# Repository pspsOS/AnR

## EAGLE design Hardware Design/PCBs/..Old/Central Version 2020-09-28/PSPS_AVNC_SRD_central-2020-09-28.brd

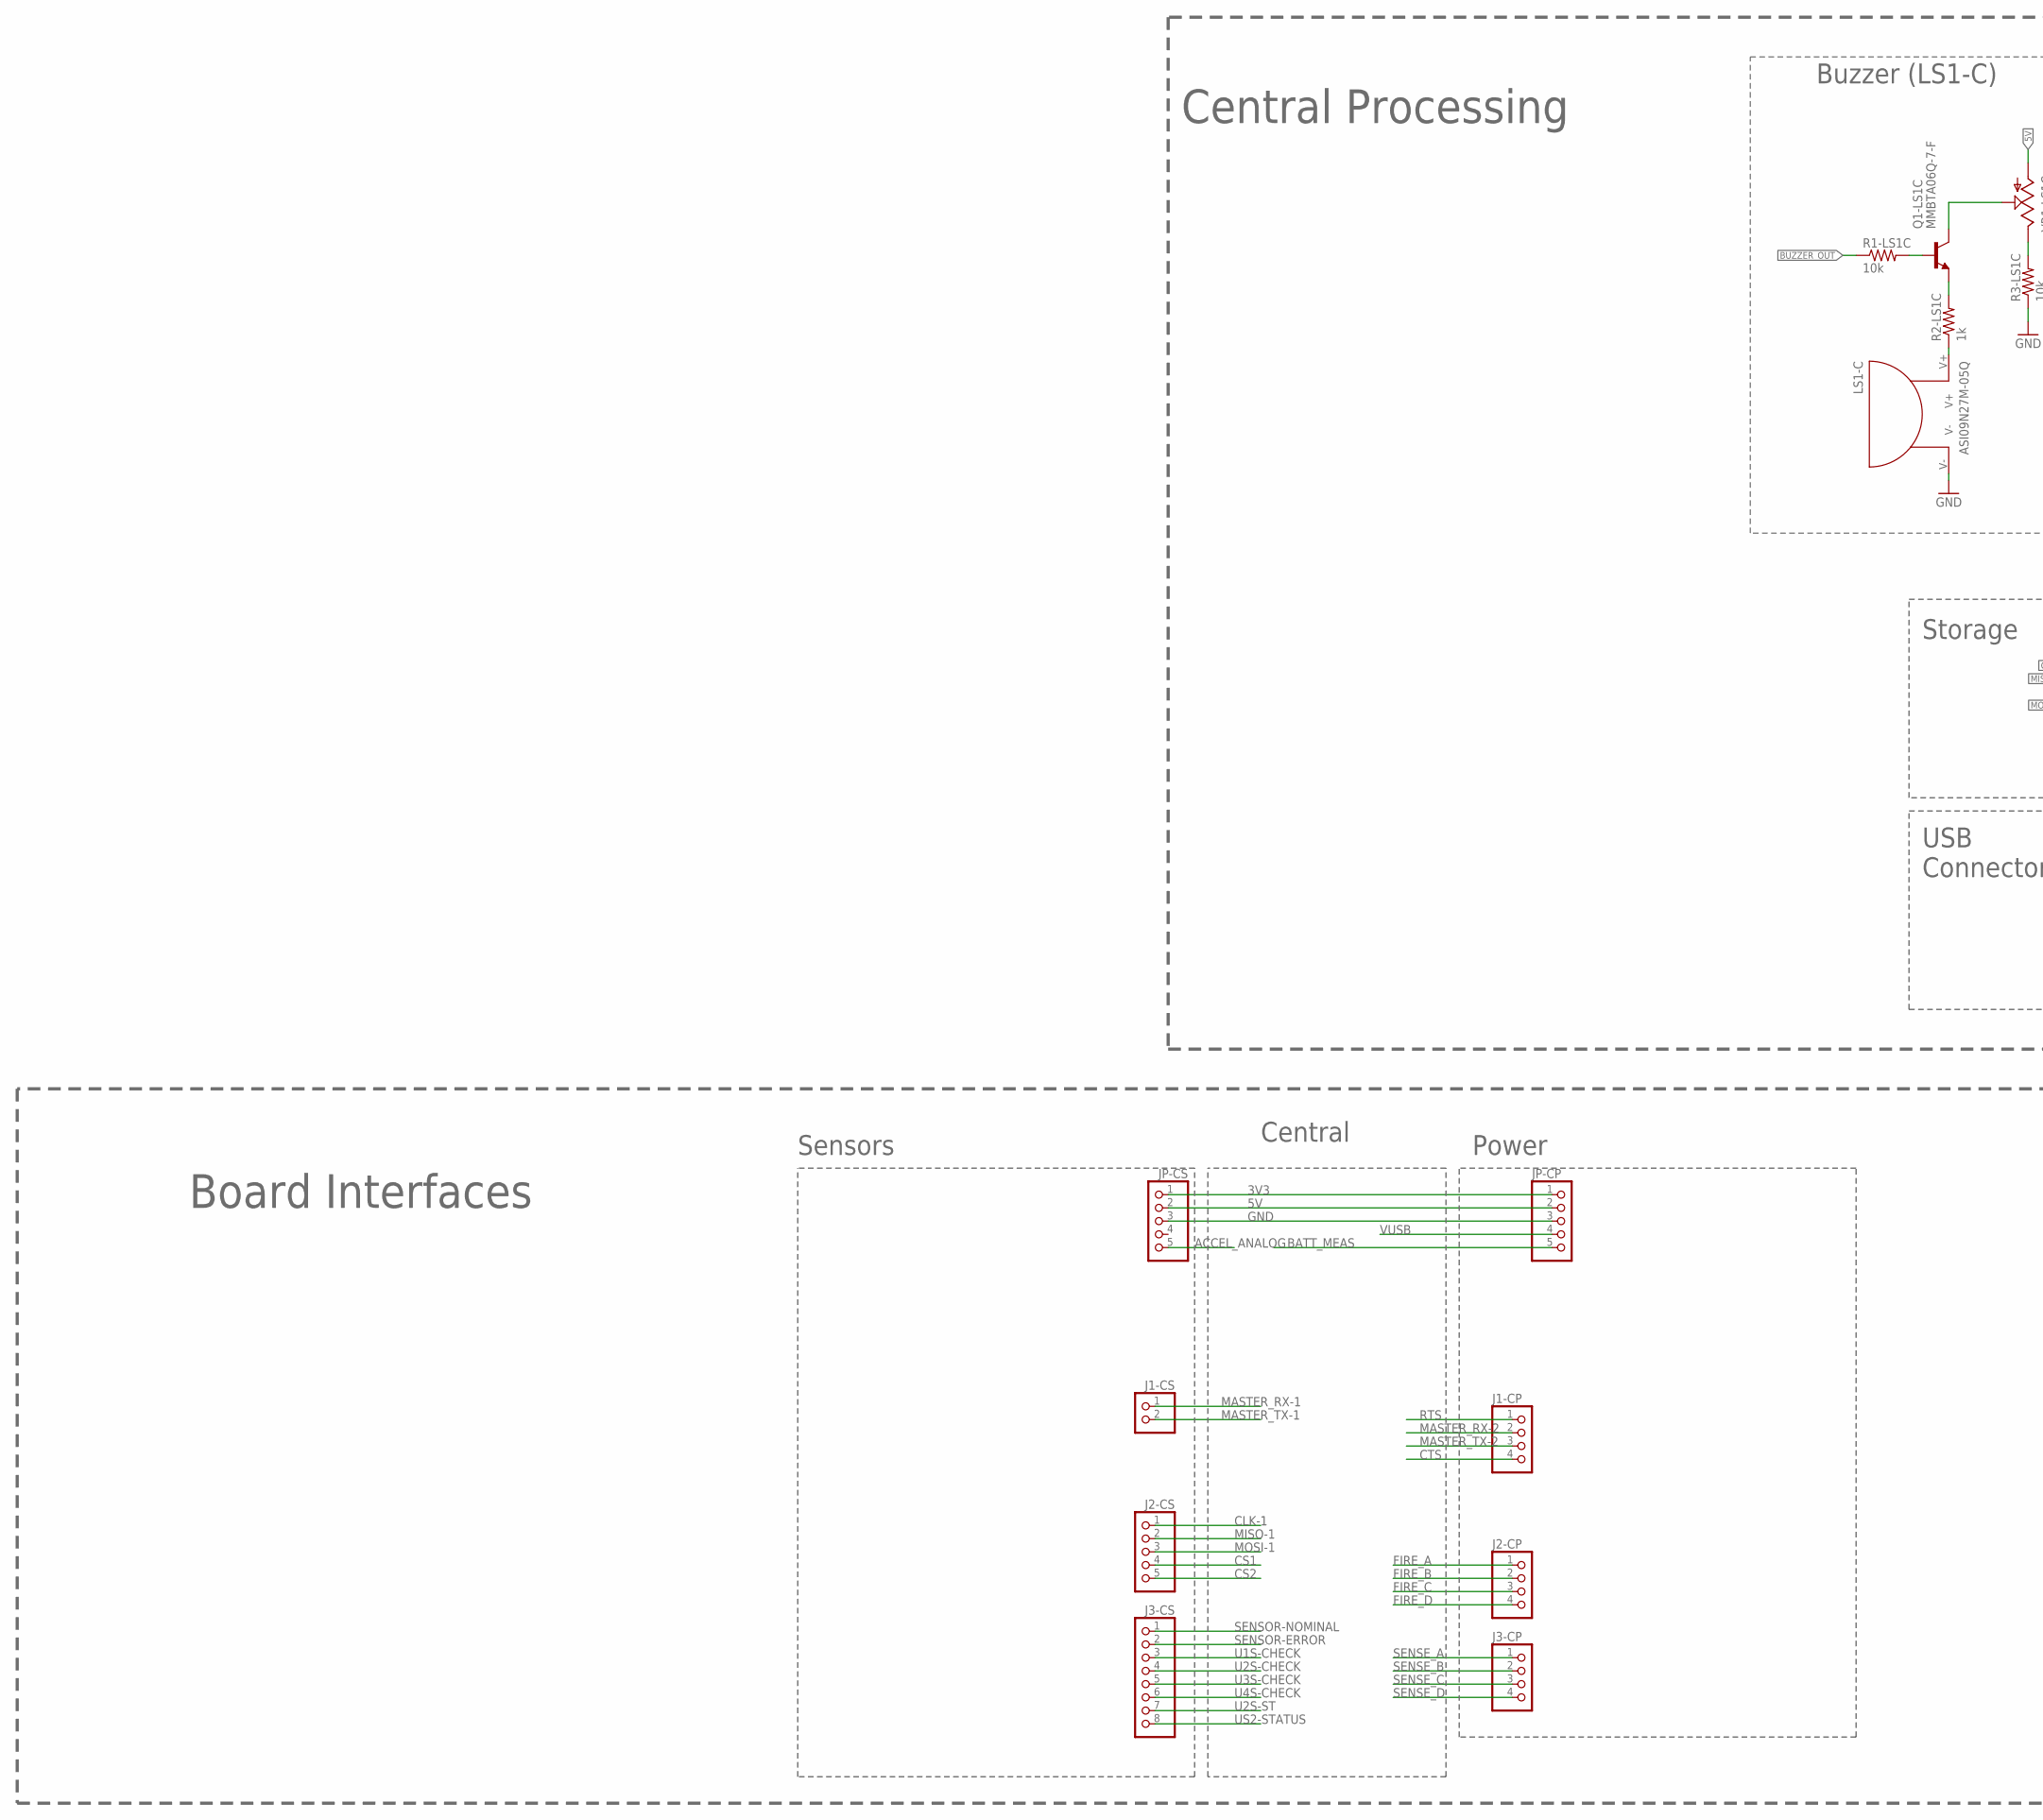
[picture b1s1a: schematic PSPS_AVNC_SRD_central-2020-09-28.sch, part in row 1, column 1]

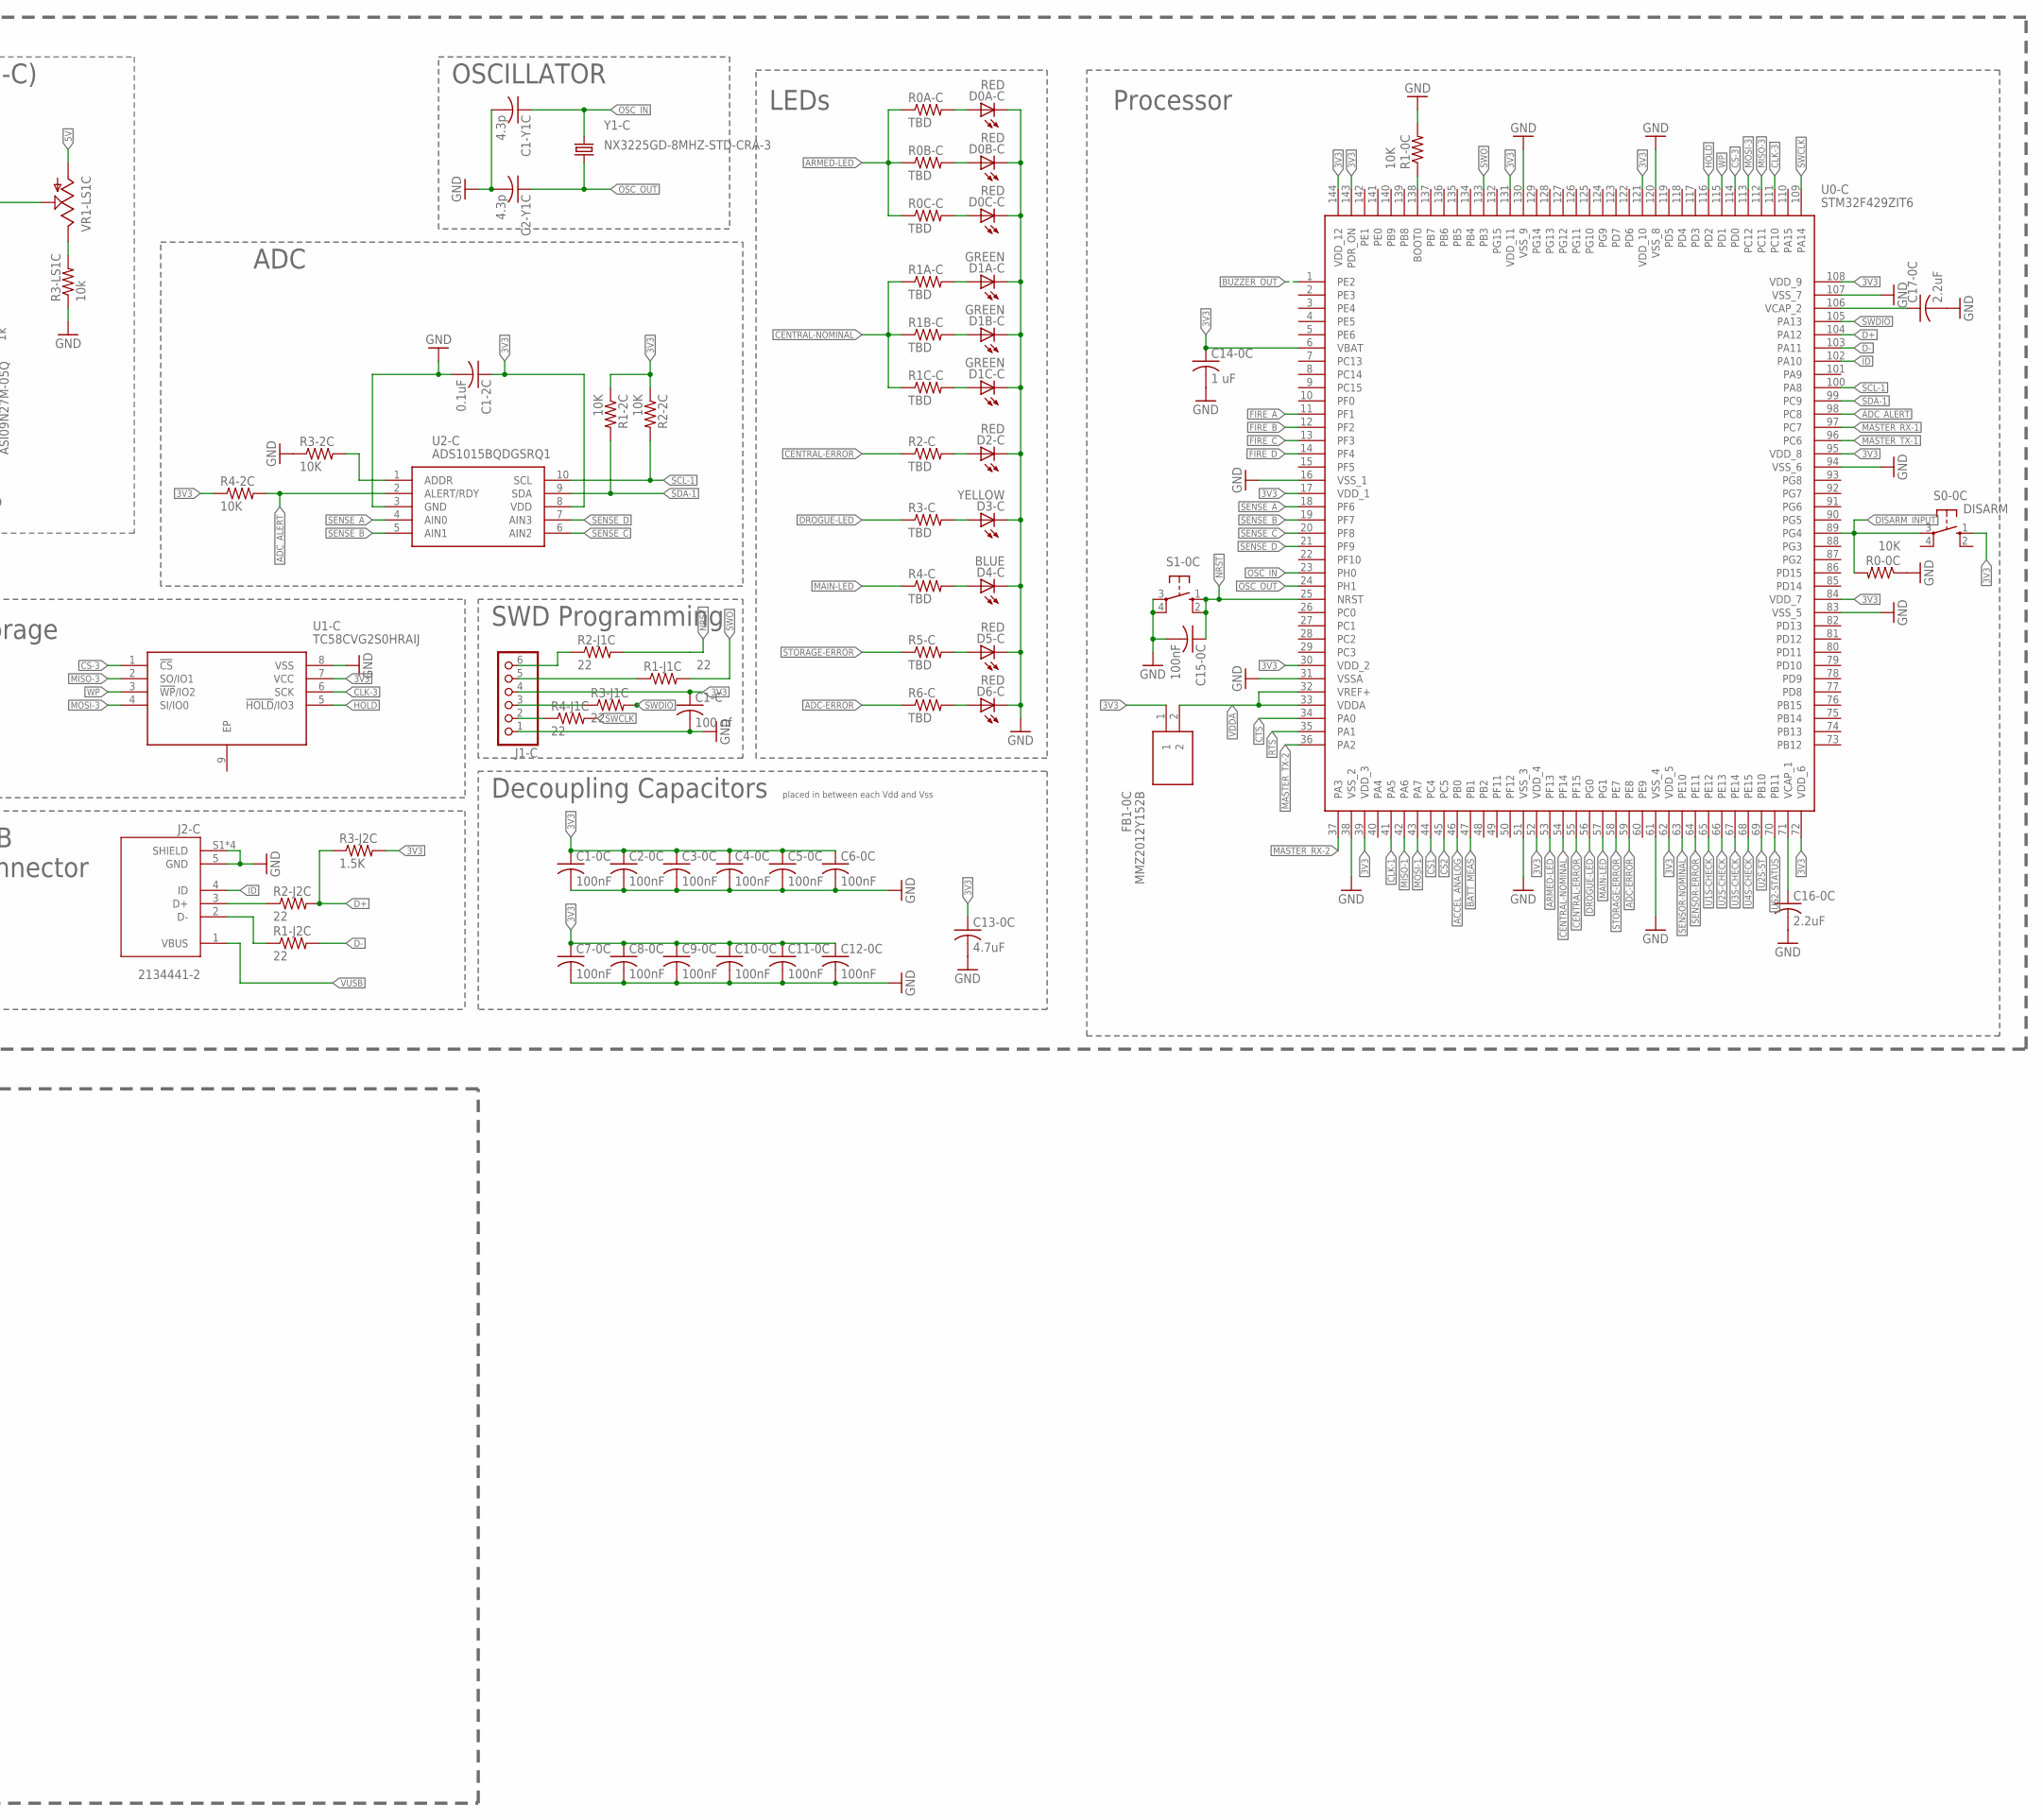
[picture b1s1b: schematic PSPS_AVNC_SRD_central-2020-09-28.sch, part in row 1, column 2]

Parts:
C1-0C, C2-0C, C3-0C, C4-0C, C5-0C, C6-0C, C7-0C, C8-0C, C9-0C, C10-0C, C11-0C, C12-0C, C15-0C: 100nF; C0805
C1-2C: 0.1uF; C0805
C1-C: 100 nf; C0805
C1-Y1C, C2-Y1C: 4.3p; C0805
C13-0C: 4.7uF; C0805
C14-0C: 1 uF; C0805
C16-0C, C17-0C: 2.2uF; C0805
D0A-C, D0B-C, D0C-C, D2-C, D5-C, D6-C: RED; CHIPLED_0805
D1A-C, D1B-C, D1C-C: GREEN; CHIPLED_0805
D3-C: YELLOW; CHIPLED_0805
D4-C: BLUE; CHIPLED_0805
FB1-0C: MMZ2012Y152B; BEADC2012X105N
J1-C: PINHD-1X6; 1X06
J1-CP, J2-CP, J3-CP: PINHD-1X4; 1X04
J1-CS: PINHD-1X2; 1X02
J2-C: 2134441-2; TE_2134441-2
J2-CS: PINHD-1X5; 1X05
J3-CS: PINHD-1X8; 1X08
JP-CP: PINHD-1X5; 1X05
JP-CS: PINHD-1X5; 1X05
LS1-C: ASI09N27M-05Q
Q1-LS1C: MMBTA06Q-7-F; SOT23
R0-0C, R1-0C, R1-2C, R2-2C, R3-2C, R4-2C: 10K; R0805
R0A-C, R0B-C, R0C-C, R1A-C, R1B-C, R1C-C, R2-C, R3-C, R4-C, R5-C, R6-C: TBD; M0805
R1-J1C, R1-J2C, R2-J1C, R2-J2C, R3-J1C, R4-J1C: 22; M0805
R1-LS1C, R3-LS1C: 10k; R0805
R2-LS1C: 1k; R0805
R3-J2C: 1.5K; M0805
S0-0C: DISARM; B3F-10XX
S1-0C: 10-XX; B3F-10XX
U0-C: STM32F429ZIT6; QFP50P2200X2200X160-144N
U1-C: TC58CVG2S0HRAIJ; SON127P800X600X80-9N
U2-C: ADS1015BQDGSRQ1; SOP50P490X110-10N
VR1-LS1C: TRIM_US-LI10; LI10
Y1-C: NX3225GD-8MHZ-STD-CRA-3; NX3225GD

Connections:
3V3: C1-0C.1, C1-2C.1, C1-C.1, C2-0C.1, C3-0C.1, C4-0C.1, C5-0C.1, C6-0C.1, C7-0C.1, C8-0C.1, C9-0C.1, C10-0C.1, C11-0C.1, C12-0C.1, C13-0C.1, C14-0C.1, FB1-0C.1, J1-C.4, JP-CP.1, JP-CS.1, R1-2C.1, R2-2C.1, R3-J2C.2, R4-2C.1, S0-0C.1 (S), U0-C.6 (VBAT), U0-C.17 (VDD_1), U0-C.30 (VDD_2), U0-C.39 (VDD_3), U0-C.52 (VDD_4), U0-C.62 (VDD_5), U0-C.72 (VDD_6), U0-C.84 (VDD_7), U0-C.95 (VDD_8), U0-C.108 (VDD_9), U0-C.121 (VDD_10), U0-C.131 (VDD_11), U0-C.143 (PDR_ON), U0-C.144 (VDD_12), U1-C.7 (VCC), U2-C.8 (VDD)
5V: JP-CP.2, JP-CS.2, VR1-LS1C.A
ACCEL_ANALOG: JP-CS.5, U0-C.46 (PB0)
ADC-ERROR: R6-C.1, U0-C.59 (PE8)
ADC_ALERT: R4-2C.2, U0-C.98 (PC8), U2-C.2 (ALERT/RDY)
ADDR: R3-2C.2, U2-C.1 (ADDR)
ARMED-LED: R0A-C.1, R0B-C.1, R0C-C.1, U0-C.53 (PF13)
BATT_MEAS: JP-CP.5, U0-C.47 (PB1)
BOOT0: R1-0C.1, U0-C.138 (BOOT0)
BUZZER_OUT: R1-LS1C.1, U0-C.1 (PE2)
CENTRAL-ERROR: R2-C.1, U0-C.55 (PF15)
CENTRAL-NOMINAL: R1A-C.1, R1B-C.1, R1C-C.1, U0-C.54 (PF14)
CLK-1: J2-CS.1, U0-C.41 (PA5)
CLK-3: U0-C.111 (PC10), U1-C.6 (SCK)
CS1: J2-CS.4, U0-C.44 (PC4)
CS2: J2-CS.5, U0-C.45 (PC5)
CS-3: U0-C.114 (PD0), U1-C.1 (!CS)
CTS: J1-CP.4, U0-C.34 (PA0)
D+: R2-J2C.2, R3-J2C.1, U0-C.104 (PA12)
D+_R2-J1C: J2-C.3 (D+), R2-J2C.1
D-: R1-J2C.2, U0-C.103 (PA11)
D-_R1-J1C: J2-C.2 (D-), R1-J2C.1
DISARM_INPUT: R0-0C.2, S0-0C.3, U0-C.89 (PG4)
DROGUE-LED: R3-C.1, U0-C.56 (PG0)
FIRE_A: J2-CP.1, U0-C.11 (PF1)
FIRE_B: J2-CP.2, U0-C.12 (PF2)
FIRE_C: J2-CP.3, U0-C.13 (PF3)
FIRE_D: J2-CP.4, U0-C.14 (PF4)
GND: C1-0C.2, C1-2C.2, C1-C.2, C1-Y1C.2, C2-0C.2, C2-Y1C.2, C3-0C.2, C4-0C.2, C5-0C.2, C6-0C.2, C7-0C.2, C8-0C.2, C9-0C.2, C10-0C.2, C11-0C.2, C12-0C.2, C13-0C.2, C14-0C.2, C15-0C.2, C16-0C.2, C17-0C.2, D0A-C.C, D0B-C.C, D0C-C.C, D1A-C.C, D1B-C.C, D1C-C.C, D2-C.C, D3-C.C, D4-C.C, D5-C.C, D6-C.C, J1-C.1, J2-C.5 (GND), J2-C.S1 (SHIELD), J2-C.S2 (SHIELD), J2-C.S3 (SHIELD), J2-C.S4 (SHIELD), JP-CP.3, JP-CS.3, LS1-C.V-, R0-0C.1, R1-0C.2, R3-2C.1, R3-LS1C.1, S1-0C.3, S1-0C.4 (P1), U0-C.16 (VSS_1), U0-C.31 (VSSA), U0-C.38 (VSS_2), U0-C.51 (VSS_3), U0-C.61 (VSS_4), U0-C.83 (VSS_5), U0-C.94 (VSS_6), U0-C.107 (VSS_7), U0-C.120 (VSS_8), U0-C.130 (VSS_9), U1-C.8 (VSS), U2-C.3 (GND)
HOLD: U0-C.116 (PD2), U1-C.5 (!HOLD!/IO3)
ID: J2-C.4 (ID), U0-C.102 (PA10)
J1-C_R1-J1C: J1-C.5, R1-J1C.1
J1-C_R2-J1C: J1-C.6, R2-J1C.1
J1-C_R3-J1C: J1-C.3, R3-J1C.1
J1-C_R4-J1C: J1-C.2, R4-J1C.1
MAIN-LED: R4-C.1, U0-C.57 (PG1)
MASTER_RX-1: J1-CS.1, U0-C.97 (PC7)
MASTER_RX-2: J1-CP.2, U0-C.37 (PA3)
MASTER_TX-1: J1-CS.2, U0-C.96 (PC6)
MASTER_TX-2: J1-CP.3, U0-C.36 (PA2)
MISO-1: J2-CS.2, U0-C.42 (PA6)
MISO-3: U0-C.112 (PC11), U1-C.2 (SO/IO1)
MOSI-1: J2-CS.3, U0-C.43 (PA7)
MOSI-3: U0-C.113 (PC12), U1-C.4 (SI/IO0)
NRST: C15-0C.1, R2-J1C.2, S1-0C.1 (S), S1-0C.2 (S1), U0-C.25 (NRST)
OSC_IN: C1-Y1C.1, U0-C.23 (PH0), Y1-C.P$2 (2)
OSC_OUT: C2-Y1C.1, U0-C.24 (PH1), Y1-C.P$1 (1)
Q1-LS1C_R2-LS1C: Q1-LS1C.3 (E), R2-LS1C.2
R0A-C_D0A-C: D0A-C.A, R0A-C.2
R0B-C_D0B-C: D0B-C.A, R0B-C.2
R0C-C_D0C-C: D0C-C.A, R0C-C.2
R1-LS1C_Q1-LS1C: Q1-LS1C.1 (B), R1-LS1C.2
R1A-C_D1A-C: D1A-C.A, R1A-C.2
R1B-C_D1B-C: D1B-C.A, R1B-C.2
R1C-C_D1C-C: D1C-C.A, R1C-C.2
R2-C_D2-C: D2-C.A, R2-C.2
R2-LS1C_LS1-C: LS1-C.V+, R2-LS1C.1
R3-C_D3-C: D3-C.A, R3-C.2
R4-C_D4-C: D4-C.A, R4-C.2
R5-C_D5-C: D5-C.A, R5-C.2
R6-C_D6-C: D6-C.A, R6-C.2
RTS: J1-CP.1, U0-C.35 (PA1)
SCL-1: R2-2C.2, U0-C.100 (PA8), U2-C.10 (SCL)
SDA-1: R1-2C.2, U0-C.99 (PC9), U2-C.9 (SDA)
SENSE_A: J3-CP.1, U0-C.18 (PF6), U2-C.4 (AIN0)
SENSE_B: J3-CP.2, U0-C.19 (PF7), U2-C.5 (AIN1)
SENSE_C: J3-CP.3, U0-C.20 (PF8), U2-C.6 (AIN2)
SENSE_D: J3-CP.4, U0-C.21 (PF9), U2-C.7 (AIN3)
SENSOR-ERROR: J3-CS.2, U0-C.64 (PE11)
SENSOR-NOMINAL: J3-CS.1, U0-C.63 (PE10)
STORAGE-ERROR: R5-C.1, U0-C.58 (PE7)
SWCLK: R4-J1C.2, U0-C.109 (PA14)
SWDIO: R3-J1C.2, U0-C.105 (PA13)
SWO: R1-J1C.2, U0-C.133 (PB3)
U1S-CHECK: J3-CS.3, U0-C.65 (PE12)
U2S-CHECK: J3-CS.4, U0-C.66 (PE13)
U2S-ST: J3-CS.7, U0-C.69 (PB10)
U3S-CHECK: J3-CS.5, U0-C.67 (PE14)
U4S-CHECK: J3-CS.6, U0-C.68 (PE15)
US2-STATUS: J3-CS.8, U0-C.70 (PB11)
VCAP_1: C16-0C.1, U0-C.71 (VCAP_1)
VCAP_2: C17-0C.1, U0-C.106 (VCAP_2)
VDDA: FB1-0C.2, U0-C.32 (VREF+), U0-C.33 (VDDA)
VR1-LS1C: Q1-LS1C.2 (C), VR1-LS1C.S
VR1-LS1C_R3-LS1C: R3-LS1C.2, VR1-LS1C.E
VUSB: J2-C.1 (VBUS), JP-CP.4
WP: U0-C.115 (PD1), U1-C.3 (!WP!/IO2)

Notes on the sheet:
Central Processing
placed in between each Vdd and Vss
Processor
Storage
Decoupling Capacitors
SWD Programming
LEDs
ADC
USB Connector
OSCILLATOR
Buzzer (LS1-C)
Central
Power
Sensors
Board Interfaces

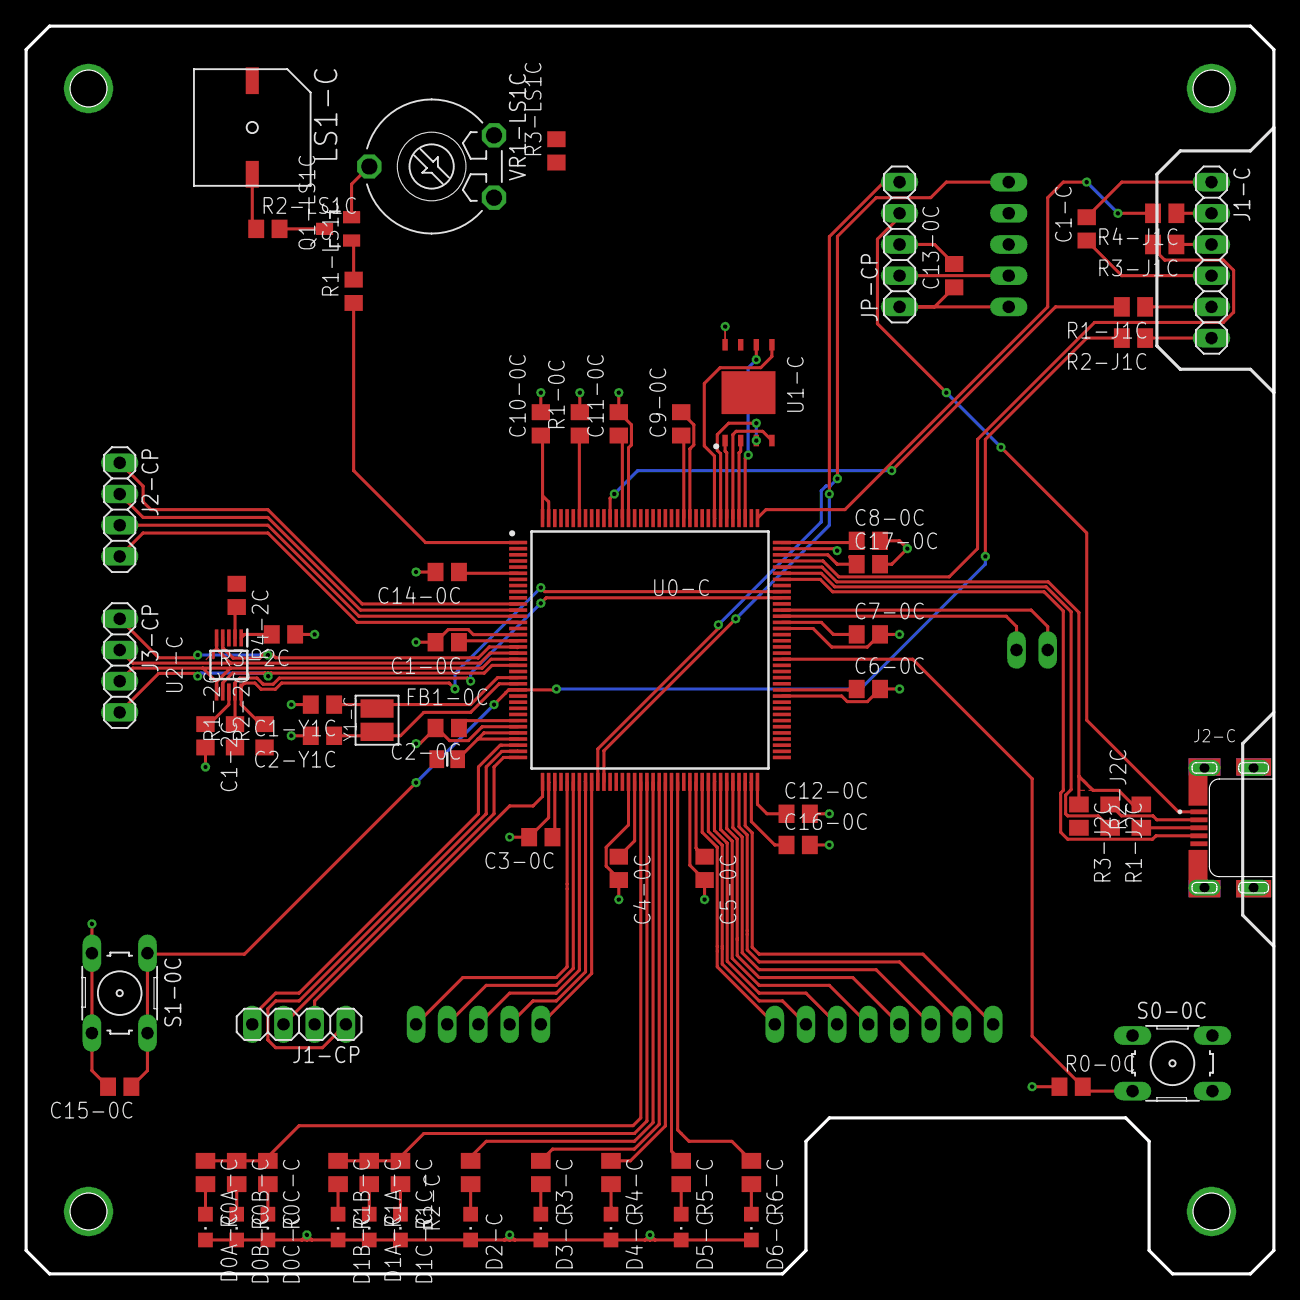
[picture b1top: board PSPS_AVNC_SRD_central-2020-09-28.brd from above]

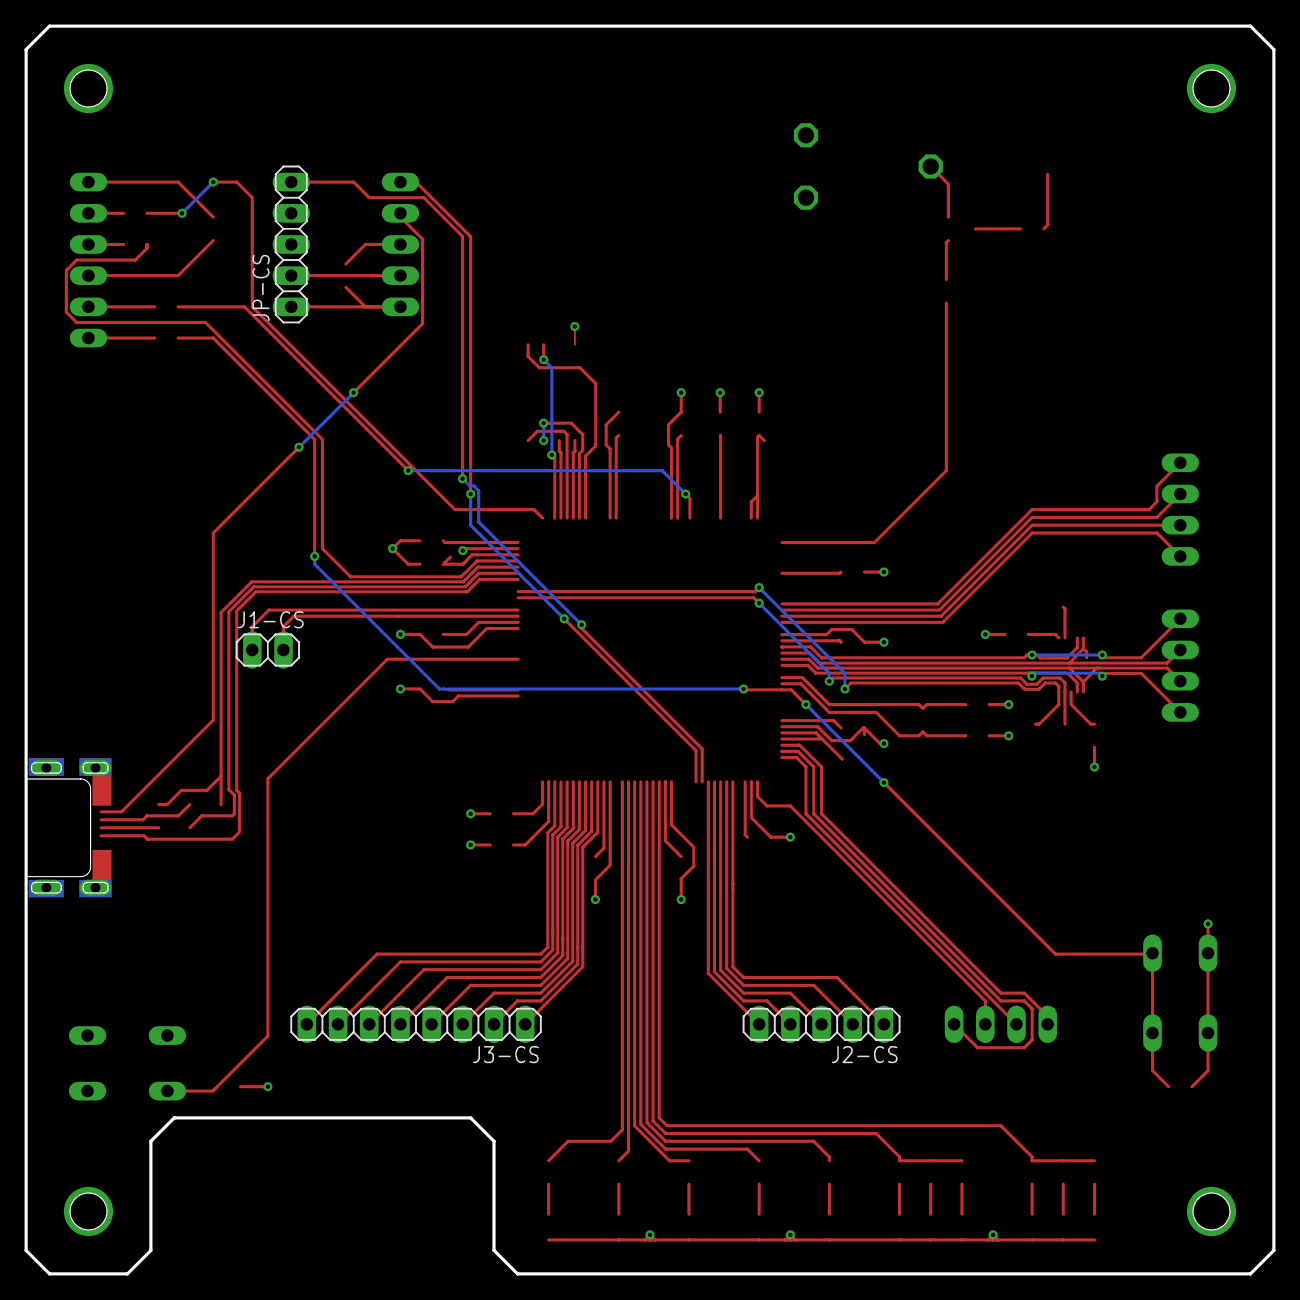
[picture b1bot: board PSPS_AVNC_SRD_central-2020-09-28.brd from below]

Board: 2 copper layers, 101.6 x 101.6 mm, 79 parts (4 on the bottom side), 87 nets.

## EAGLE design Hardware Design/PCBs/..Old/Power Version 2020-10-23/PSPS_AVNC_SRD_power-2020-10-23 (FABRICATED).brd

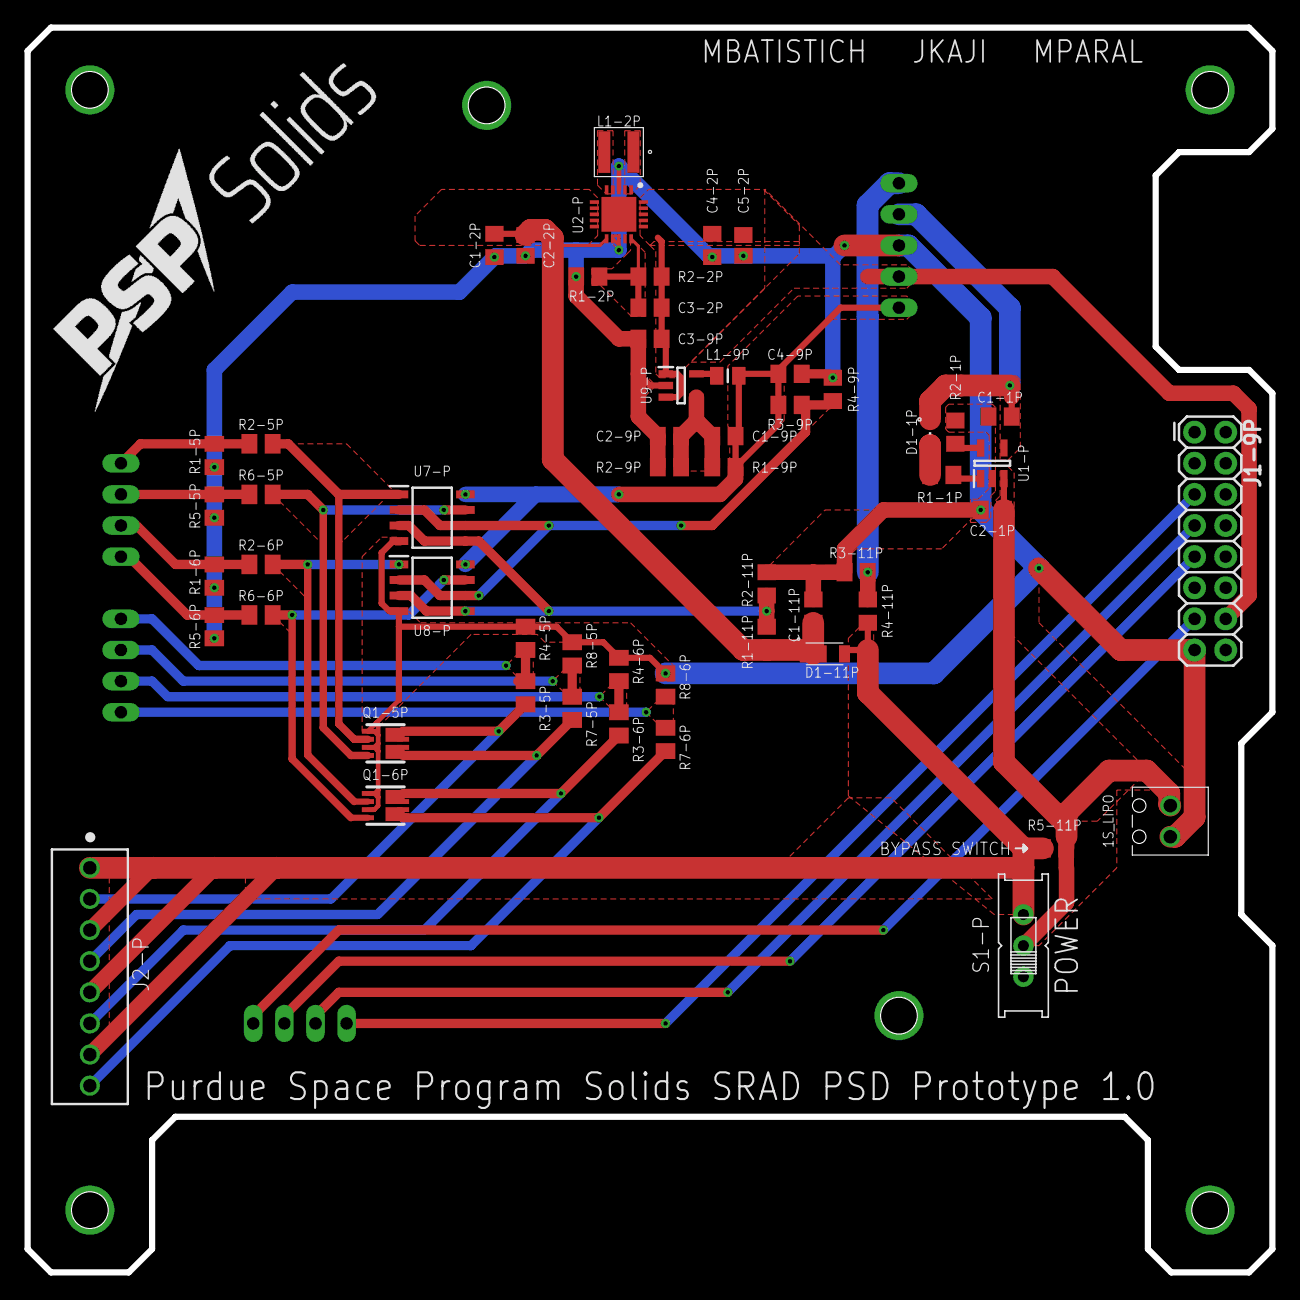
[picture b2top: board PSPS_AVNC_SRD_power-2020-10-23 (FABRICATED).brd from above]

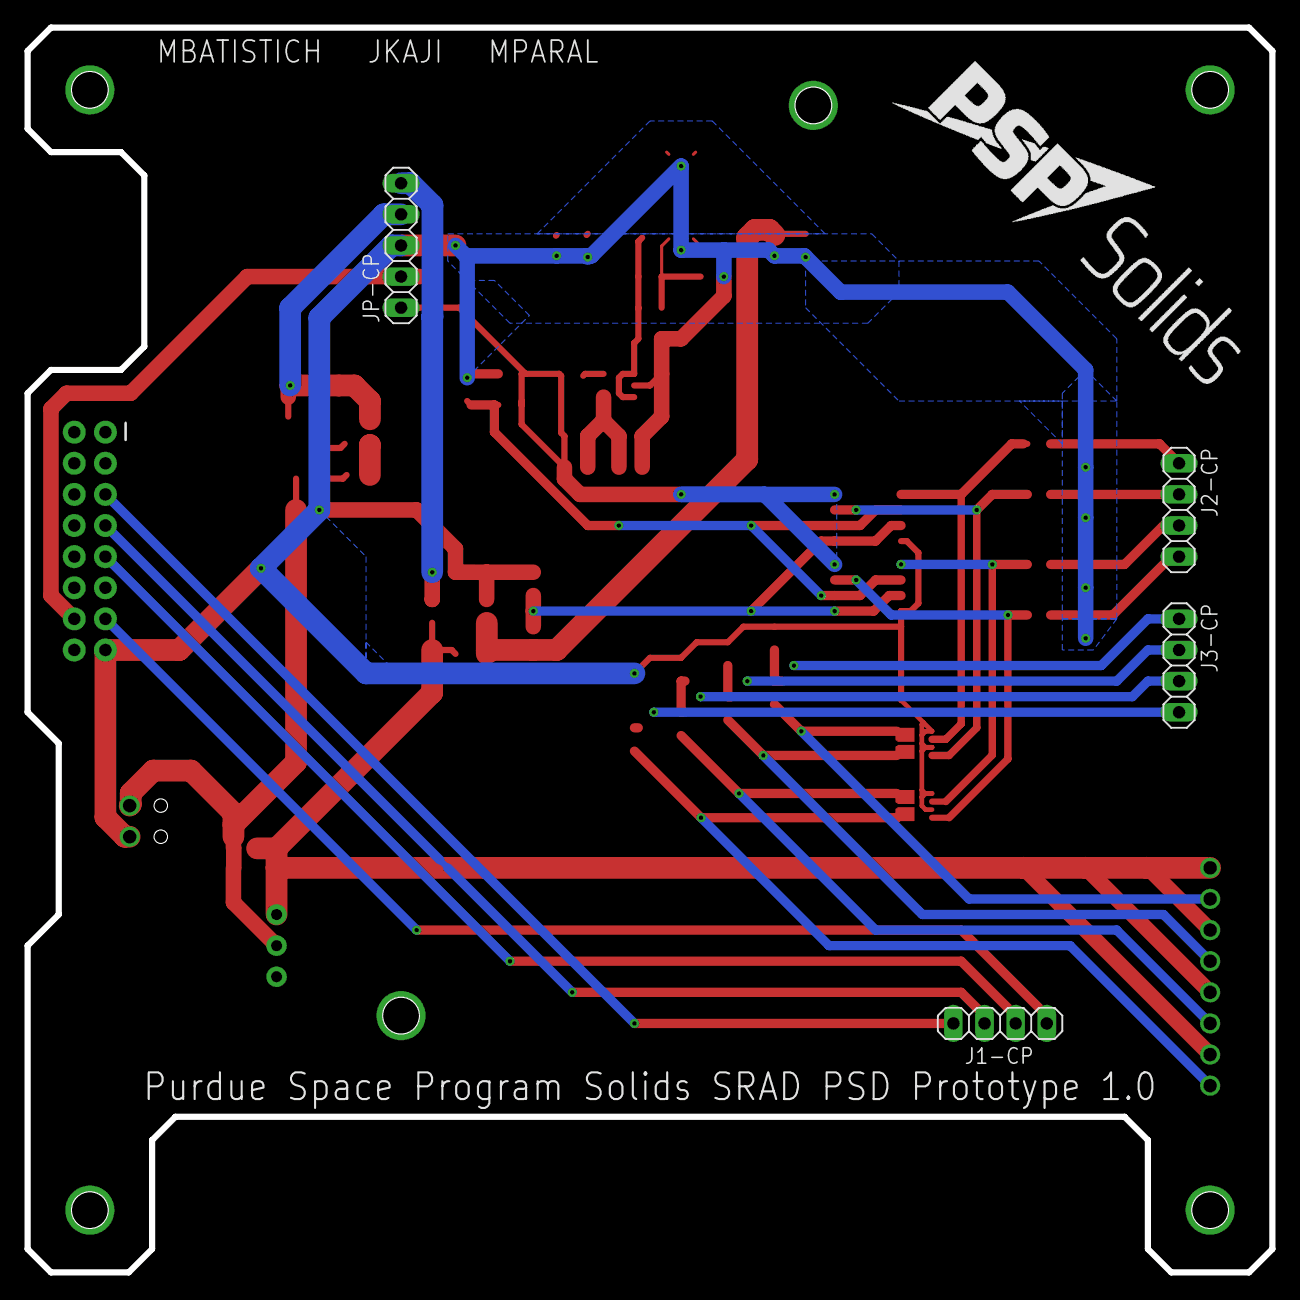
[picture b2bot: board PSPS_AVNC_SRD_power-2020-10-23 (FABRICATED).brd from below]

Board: 2 copper layers, 101.6 x 101.6 mm, 60 parts (4 on the bottom side), 38 nets.

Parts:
1S_LIPO: 1725656
C1-1P, C2-1P: 4.7uF; C0805
C1-2P, C2-2P, C4-9P: 10uF; C0805
C1-9P: 33pF; C0805
C1-11P: 47uF; C0805
C2-9P: 6.8pF; C0805
C3-2P, C4-2P, C5-2P: 22pF; C0805
C3-9P: 4.7pF; C0805
D1-1P: GREEN; CHIPLED_0805
D1-11P: DFLS130L-7 (TBD); POWERDI_123
J1-9P: 2X8
J1-CP, J2-CP, J3-CP: 1X04
J2-P: 1725711
JP-CP: 1X05
L1-2P: XFL4020-102MEB (1uH); XFL4020
L1-9P: LQM21PH2R2NGCD (2.2uH); INDC2012X100N
Q1-5P, Q1-6P: SI7232DN-T1-GE3; POWERPAK-1212-8
R1-1P: 12k; R0805
R1-2P: 187k; R0805
R1-5P, R1-6P, R5-5P, R5-6P: 3.3K; M0805
R1-9P: 562k; R0805
R1-11P, R3-9P: 10k; R0805
R2-1P: 2K; R0805
R2-2P: 35.6k; R0805
R2-5P, R2-6P, R6-5P, R6-6P: 1K; M0805
R2-9P, R3-11P, R4-11P: 100k; R0805
R2-11P: 8.06k; R0805
R3-5P, R3-6P, R7-5P, R7-6P: 100K; M0805
R4-5P, R4-6P, R8-5P, R8-6P: 27K; M0805
R4-9P: 9.09k; R0805
R5-11P: 0k; R0805
S1-P: EG1218
U1-P: MCP73831; SOT95P270X145-5N
U2-P: ISL91110IRAZ-T7A; QFN50P400X400X100-21N
U7-P, U8-P: LM293DR; SOIC127P600X175-8N
U9-P: LM3671-ADJ; SOT95P280X145-5N

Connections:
3V3: C1-9P.1, C4-9P.1, JP-CP.1, L1-9P.2, R1-9P.2, R3-9P.2, U7-P.8, U8-P.8
5V: C3-2P.1, C3-9P.1, C4-2P.1, C5-2P.1, J1-9P.14, JP-CP.2, R1-2P.2, U2-P.17, U9-P.1, U9-P.3
BATT_MEAS: JP-CP.5, R3-11P.1, R4-11P.2
CMP_LDO_IN: R1-11P.1, R2-11P.2, U7-P.3, U7-P.5, U8-P.3, U8-P.5
CMP_LDO_OUT_1: Q1-5P.2, R2-5P.2, U7-P.1
CMP_LDO_OUT_2: Q1-5P.4, R6-5P.2, U7-P.7
CMP_LDO_OUT_3: Q1-6P.2, R2-6P.2, U8-P.1
CMP_LDO_OUT_4: Q1-6P.4, R6-6P.2, U8-P.7
CMP_RAIL: R3-9P.1, R4-9P.2, U7-P.2, U7-P.6, U8-P.2, U8-P.6
CTS: J1-9P.13, J1-CP.4
D1-1P_R1-1P: D1-1P.C, R1-1P.1
FET_A: J2-P.2, Q1-5P.7, Q1-5P.8, R3-5P.1
FET_B: J2-P.4, Q1-5P.5, Q1-5P.6, R7-5P.1
FET_C: J2-P.6, Q1-6P.7, Q1-6P.8, R3-6P.1
FET_D: J2-P.8, Q1-6P.5, Q1-6P.6, R7-6P.1
FIRE_A: J2-CP.1, R1-5P.2, R2-5P.1
FIRE_B: J2-CP.2, R5-5P.2, R6-5P.1
FIRE_C: J2-CP.3, R1-6P.2, R2-6P.1
FIRE_D: J2-CP.4, R5-6P.2, R6-6P.1
GND: 1S_LIPO.2, C1-1P.2, C1-2P.2, C1-11P.2, C2-1P.2, C2-2P.2, C2-9P.2, C3-9P.2, C4-2P.2, C4-9P.2, C5-2P.2, J1-9P.15, JP-CP.3, Q1-5P.1, Q1-5P.3, Q1-6P.1, Q1-6P.3, R1-5P.1, R1-6P.1, R2-1P.1, R2-2P.1, R2-9P.1, R2-11P.1, R3-11P.2, R4-5P.1, R4-6P.1, R4-9P.1, R5-5P.1, R5-6P.1, R8-5P.1, R8-6P.1, U1-P.2, U2-P.3, U2-P.12, U2-P.13, U7-P.4, U8-P.4, U9-P.2
MASTER_RX-2: J1-9P.7, J1-CP.2
MASTER_TX-2: J1-9P.9, J1-CP.3
RTS: J1-9P.5, J1-CP.1
SENSE_A: J3-CP.1, R3-5P.2, R4-5P.2
SENSE_B: J3-CP.2, R7-5P.2, R8-5P.2
SENSE_C: J3-CP.3, R3-6P.2, R4-6P.2
SENSE_D: J3-CP.4, R7-6P.2, R8-6P.2
U1P-PROG: R2-1P.2, U1-P.5
U1P-STAT: R1-1P.2, U1-P.1
U2P-FB: C3-2P.2, R1-2P.1, R2-2P.2, U2-P.15
U9P-FB: C1-9P.2, C2-9P.1, R1-9P.1, R2-9P.2, U9-P.4
U9P-LX1: L1-2P.2, U2-P.4, U2-P.5
U9P-LX2: L1-2P.1, U2-P.1, U2-P.2
U9P-SW: L1-9P.1, U9-P.5
VBAT: 1S_LIPO.1, C2-1P.1, R5-11P.1, S1-P.P, U1-P.3
VBAT_AFTER_SWITCH: D1-11P.2, J2-P.1, J2-P.3, J2-P.5, J2-P.7, R4-11P.1, R5-11P.2, S1-P.S
VUSB: C1-1P.1, D1-1P.A, JP-CP.4, U1-P.4
V_LDO_IN: C1-2P.1, C1-11P.1, C2-2P.1, D1-11P.1, R1-11P.2, U2-P.6, U2-P.10, U2-P.11

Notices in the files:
parts and their libraries:
SparkFun-Connectors: Licensing: Creative Commons ShareAlike 4.0 International - https://creativecommons.org/licenses/by-sa/4.0
